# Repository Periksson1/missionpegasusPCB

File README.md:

# Mission Pegasus

PCB and mechanical design files for Mission Pegasus: a Raspberry Pi Zero carrier
and an AMS AS7265x spectral sensor board, designed to mate at 90°. The repository
includes schematics, PCB layouts, custom component libraries, mechanical CAD,
modal-analysis project files, and bills of materials.

## PDF schematics

Browse the current schematics without installing KiCad:

- [Main-board schematic (PDF)](output/pdf/main-board-schematic.pdf) - Raspberry Pi, stack interface, programming, and sensor connectors.
- [Sensor-board schematic (PDF)](output/pdf/sensor-board-schematic.pdf) - AS7265x sensors, flash, and board connector.

These are vector PDF exports of the current board schematics. Zoom in for pin
labels and component values. Regenerate the PDFs whenever the source schematics change.

## 3D CAD previews

These views are rendered from the KiCad PCB files and their associated 3D models.

### Main board

[Open the main-board project](main-board/Mission%20Pegasus.kicad_pro).

### Sensor board

[Open the sensor-board project](mezzanine-board/sensorPCB.kicad_pro).
For the mechanical assembly, see the [STEP export](CAD/PCBAssemblyFEA.stp)
and [Inventor CAD files](CAD/).

## Current design and status

The current design is on **[`main`](https://github.com/Periksson1/missionpegasusPCB/tree/main)**.
This is the default branch shown when you open the repository on GitHub.

Both boards have KiCad schematics and PCB layouts. CAD assemblies and an ANSYS
modal-analysis project are included. Manufacturing, assembly, electrical test,
and analysis pass/fail results are **not documented here yet**; the presence of
these files does not establish that the hardware has been validated.

## Getting started

1. Install **KiCad 10.0 or newer**. Both PCB files were saved with KiCad 10.0.
2. Clone the current design:

   ```sh
   git clone --branch main https://github.com/Periksson1/missionpegasusPCB.git
   cd missionpegasusPCB
   ```

3. Open `main-board/Mission Pegasus.kicad_pro` or
   `mezzanine-board/sensorPCB.kicad_pro` in KiCad's project manager.
4. Keep the project folders and their `libraries/` directories together. Custom
   library tables use `${KIPRJMOD}` paths; standard KiCad libraries are also needed.

For mechanical work, `.iam` and `.ipt` files are Autodesk Inventor assemblies and
parts. STEP (`.step` / `.stp`) exports are supplied for compatible CAD viewers.
`Analysis/ModalAnalysis.wbpj` is an ANSYS Workbench project; retain its adjacent
`ModalAnalysis_files/` directory. Exact Inventor and ANSYS application requirements
have not been documented.

## Boards

| Project | Description | Documentation |
|---|---|---|
| [Main board](main-board/Mission%20Pegasus.kicad_pro) | Raspberry Pi Zero carrier and stack interface | [Main-board README](main-board/README.md) |
| [Mezzanine board](mezzanine-board/sensorPCB.kicad_pro) | Spectral sensor daughterboard for the perpendicular assembly | [Mezzanine README](mezzanine-board/README.md) |

## Repository layout

| Path | Contents |
|---|---|
| `main-board/` | Main-board KiCad project, local libraries, documentation, BOMs, and CAD exports |
| `mezzanine-board/` | Sensor-board KiCad project, local libraries, BOMs, and CAD exports |
| `CAD/` | Mechanical assemblies, bracket parts, and assembly STEP export |
| `Analysis/` | ANSYS Workbench modal-analysis project and supporting files |
| `Combined BOM.xlsx` | Combined bill of materials |
| `Peter's Files/` | Additional copies of board projects, CAD, BOMs, and vendor software; use the top-level board folders for the documented workflow |
| `vendor/` | Third-party AMS dashboard software, firmware, and FTDI driver files |
| `MEZZANINE_INTERFACE.md` | Draft connector/interface planning notes with incomplete pin assignments |

The relationship and revision differences between `Peter's Files/` and the
top-level projects have not been reconciled in this documentation.

## BOMs and design references

- [Combined BOM](Combined%20BOM.xlsx)
- [Main-board BOM](main-board/Mission%20PegasusBOM.csv)
- [Sensor-board BOM](mezzanine-board/sensorPCBBOM.csv)
- [Component notes](main-board/docs/Components.docx) and [datasheets](main-board/docs/datasheets/)
- [Stack-interface schematic](main-board/StackInterface.kicad_sch)
- [Draft mezzanine interface](MEZZANINE_INTERFACE.md)
- [Mechanical assembly STEP export](CAD/PCBAssemblyFEA.stp)

BOMs and CAD exports are saved snapshots. Check them against the chosen board
revision before ordering parts or manufacturing. The interface document still
contains `TBD` pins; use the current schematics and verify connector numbering
and mechanical orientation before connecting hardware.

## Editing the designs

The main-board schematic contains cached versions of `AS72652`, `AS72653`, and
`RASPBERRY_PI_ZERO_2_W`. As noted in the [main-board documentation](main-board/README.md),
the corresponding library copies are older/incomplete. **Do not run
Tools → Update Symbols from Library on these parts** without first reconciling
the library definitions with the schematic.

When preparing a hardware revision, record its ERC/DRC results, fabrication
revision, assembly status, and test results alongside the design so readers can
distinguish design work from validated hardware.

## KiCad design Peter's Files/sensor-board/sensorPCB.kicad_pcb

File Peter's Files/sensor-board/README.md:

# Mezzanine board (90°)

Daughterboard that mates **perpendicular** to the Mission Pegasus main board
via the shared 2x26 (2.54 mm) stack connector.

> Status: not started — create the KiCad project into this folder (see below).

## Creating the project

1. In KiCad: **File → New Project…**
2. Save it **inside this `mezzanine-board/` folder** (e.g. `Mezzanine.kicad_pro`).
   Keep "Create a new folder" **unchecked** so the files land here directly.
3. Custom parts go in the pre-made `libraries/` subfolders:
   - `libraries/footprints/` (`.pretty`)
   - `libraries/symbols/` (`.kicad_sym`)
   - `libraries/3dmodels/` (`.3dshapes`)
   Register them in this project's `fp-lib-table` / `sym-lib-table` using
   `${KIPRJMOD}/libraries/...` paths so the board stays self-contained.

## The 90° mating interface

- Use the **same connector part and pinout** as the main board's stack
  interface (see `../main-board/StackInterface.kicad_sch`). Pin 1 must meet
  pin 1.
- For the right-angle mate, typically one board carries a **right-angle**
  header and the other a vertical socket. Decide which side is which.
- Match the **connector position and board outline** so the boards align
  physically. Verify by exporting STEP from both boards and checking the
  perpendicular fit in a 3D view.

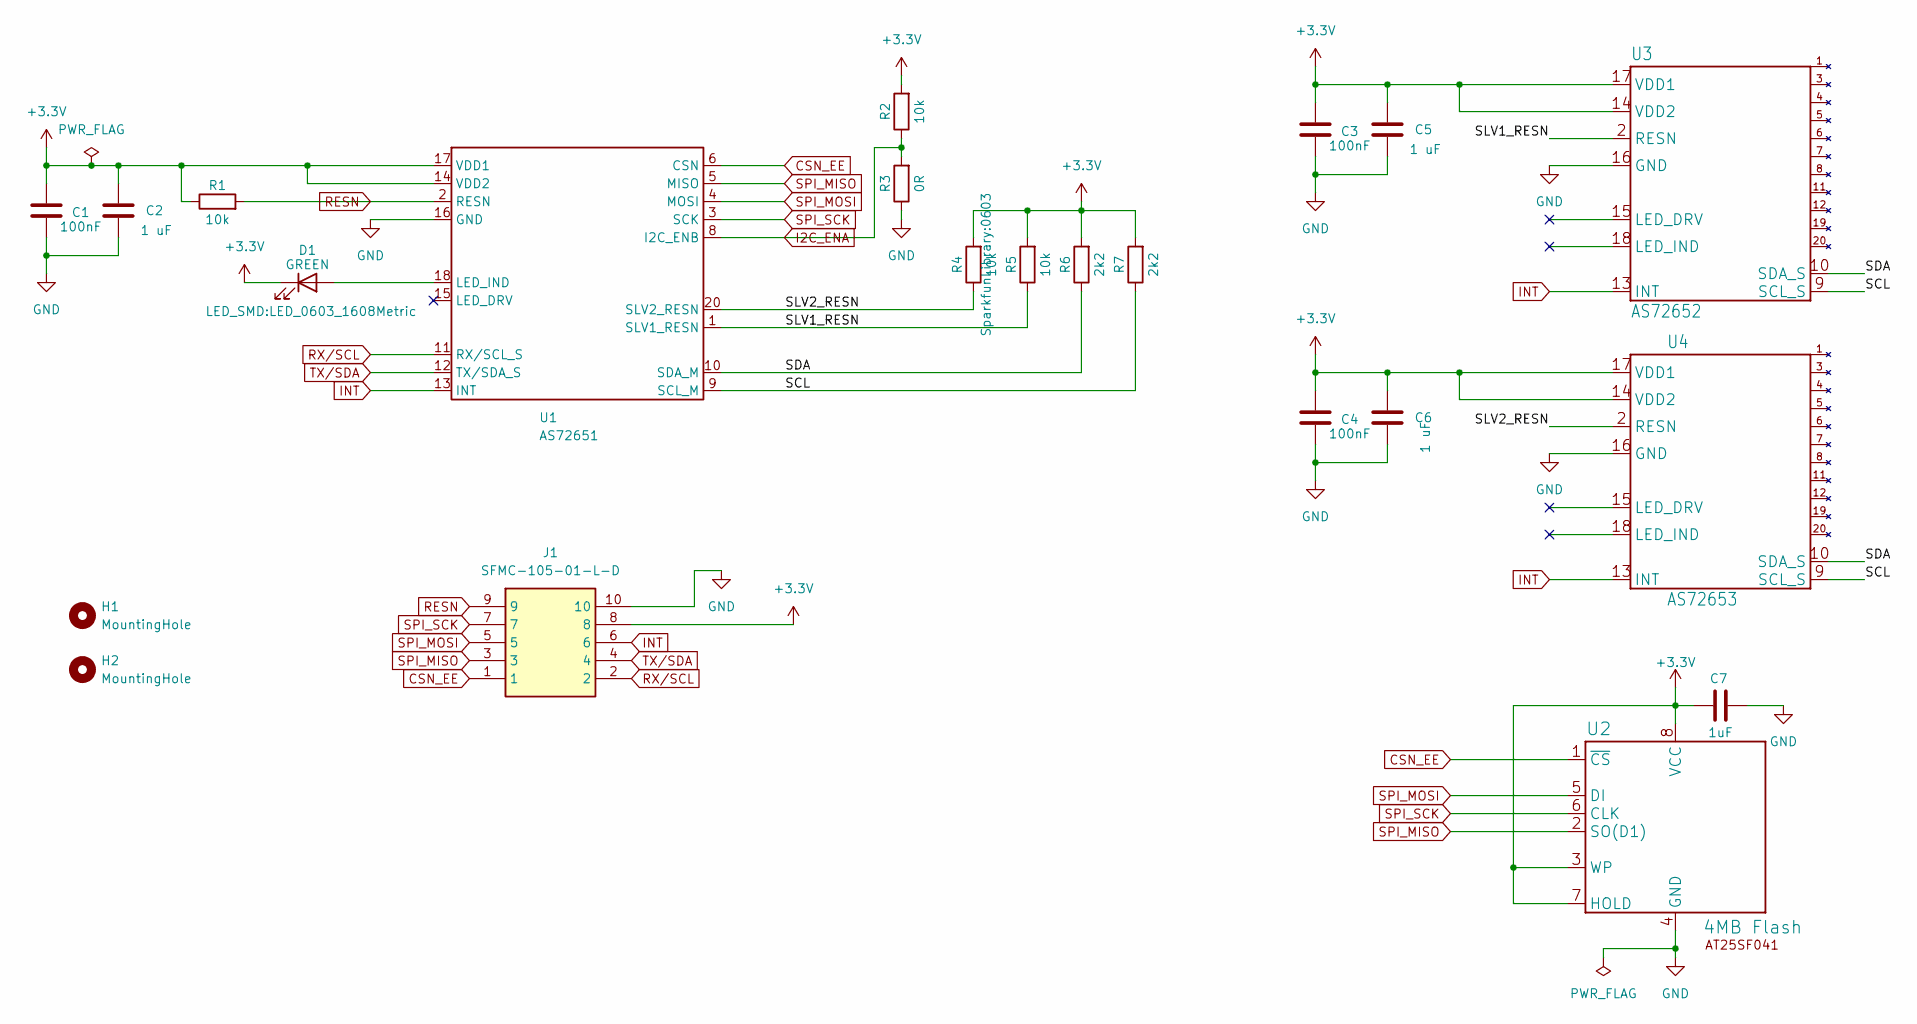
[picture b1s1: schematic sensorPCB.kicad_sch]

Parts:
C1, C3, C4: 100nF; 0603
C2, C5, C6: 1 uF; 0603
C7: 1uF; 0603
D1: GREEN; LED_0603_1608Metric
H1, H2: MountingHole; MountingHole_3.7mm
J1: SFMC-105-01-L-D; SFMC-105-XX-YY-D; Manufacturer_Part_Number SFMC-105-01-L-D; Mouser Part Number 200-SFMC10501LD
R1, R2, R4, R5: 10k; 0603
R3: 0R; 0603
R6, R7: 2k2; 0603
U1: AS72651; AS72651BLGT
U2: 4MB Flash; 4MbFlash
U3: AS72652; AS72651BLGT
U4: AS72653; AS72651BLGT

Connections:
+3.3V: C1.1, C2.1, C3.1, C4.1, C5.1, C6.1, C7.1, D1.1 (K), J1.8, R1.1, R2.2, R4.2, R5.2, R6.2, R7.2, U1.14 (VDD2), U1.17 (VDD1), U2.3 (WP), U2.7 (HOLD), U2.8 (VCC), U3.14 (VDD2), U3.17 (VDD1), U4.14 (VDD2), U4.17 (VDD1)
/SCL: R7.1, U1.9 (SCL_M), U3.9 (SCL_S), U4.9 (SCL_S)
/SDA: R6.1, U1.10 (SDA_M), U3.10 (SDA_S), U4.10 (SDA_S)
/SLV1_RESN: R5.1, U1.1 (SLV1_RESN), U3.2 (RESN)
/SLV2_RESN: R4.1, U1.20 (SLV2_RESN), U4.2 (RESN)
CSN_EE: J1.1, U1.6 (CSN), U2.1 (~CS)
GND: C1.2, C2.2, C3.2, C4.2, C5.2, C6.2, C7.2, J1.10, R3.1, U1.16 (GND), U2.4 (GND), U3.16 (GND), U4.16 (GND)
I2C_ENA: R2.1, R3.2, U1.8 (I2C_ENB)
INT: J1.6, U1.13 (INT), U3.13 (INT), U4.13 (INT)
unnamed: D1.2 (A), U1.18 (LED_IND)
RESN: J1.9, R1.2, U1.2 (RESN)
RX/SCL: J1.2, U1.11 (RX/SCL_S)
SPI_MISO: J1.3, U1.5 (MISO), U2.2 (SO(D1))
SPI_MOSI: J1.5, U1.4 (MOSI), U2.5 (DI)
SPI_SCK: J1.7, U1.3 (SCK), U2.6 (CLK)
TX/SDA: J1.4, U1.12 (TX/SDA_S)

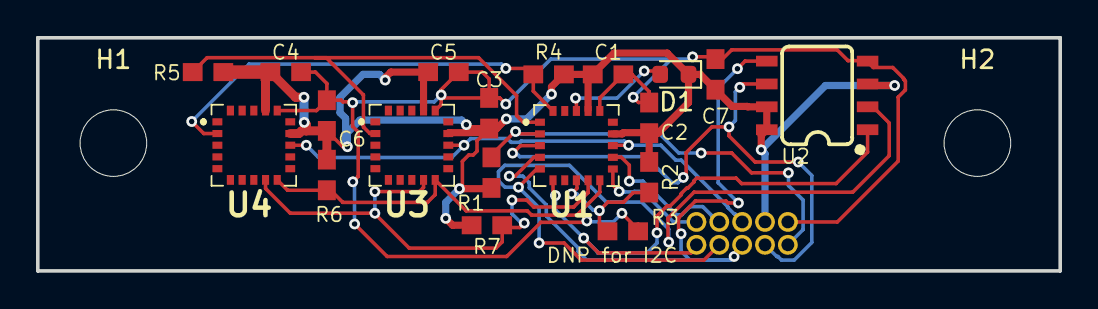
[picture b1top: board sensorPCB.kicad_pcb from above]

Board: 2 copper layers, 56.8 x 13.0 mm, 22 parts (1 on the bottom side), 16 nets.

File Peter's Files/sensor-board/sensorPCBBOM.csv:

"Reference","Qty","Value","DNP","Exclude from BOM","Exclude from Board","Footprint","Datasheet"
"C1,C3,C4","3","100nF","","","","SparkfunLibrary:0603",""
"C2,C5,C6","3","1 uF","","","","SparkfunLibrary:0603",""
"C7","1","1uF","","","","SparkfunLibrary:0603",""
"D1","1","GREEN","","","","LED_SMD:LED_0603_1608Metric",""
"J1","1","SFMC-105-01-L-D","","","","SamacSys_Parts:SFMC-105-XX-YY-D","http://suddendocs.samtec.com/prints/sfmc-1xx-xx-xx-d-xx-mkt.pdf"
"R1,R2,R4,R5","4","10k","","","","SparkfunLibrary:0603",""
"R3","1","0R","","","","SparkfunLibrary:0603",""
"R6,R7","2","2k2","","","","SparkfunLibrary:0603",""
"U1","1","AS72651","","","","SamacSys_Parts:AS72651BLGT","https://ams.com/documents/20143/36005/AS7265x_DS000612_1-00.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"
"U2","1","4MB Flash","","","","SparkfunLibrary:4MbFlash",""
"U3","1","AS72652","","","","SamacSys_Parts:AS72651BLGT",""
"U4","1","AS72653","","","","SamacSys_Parts:AS72651BLGT",""

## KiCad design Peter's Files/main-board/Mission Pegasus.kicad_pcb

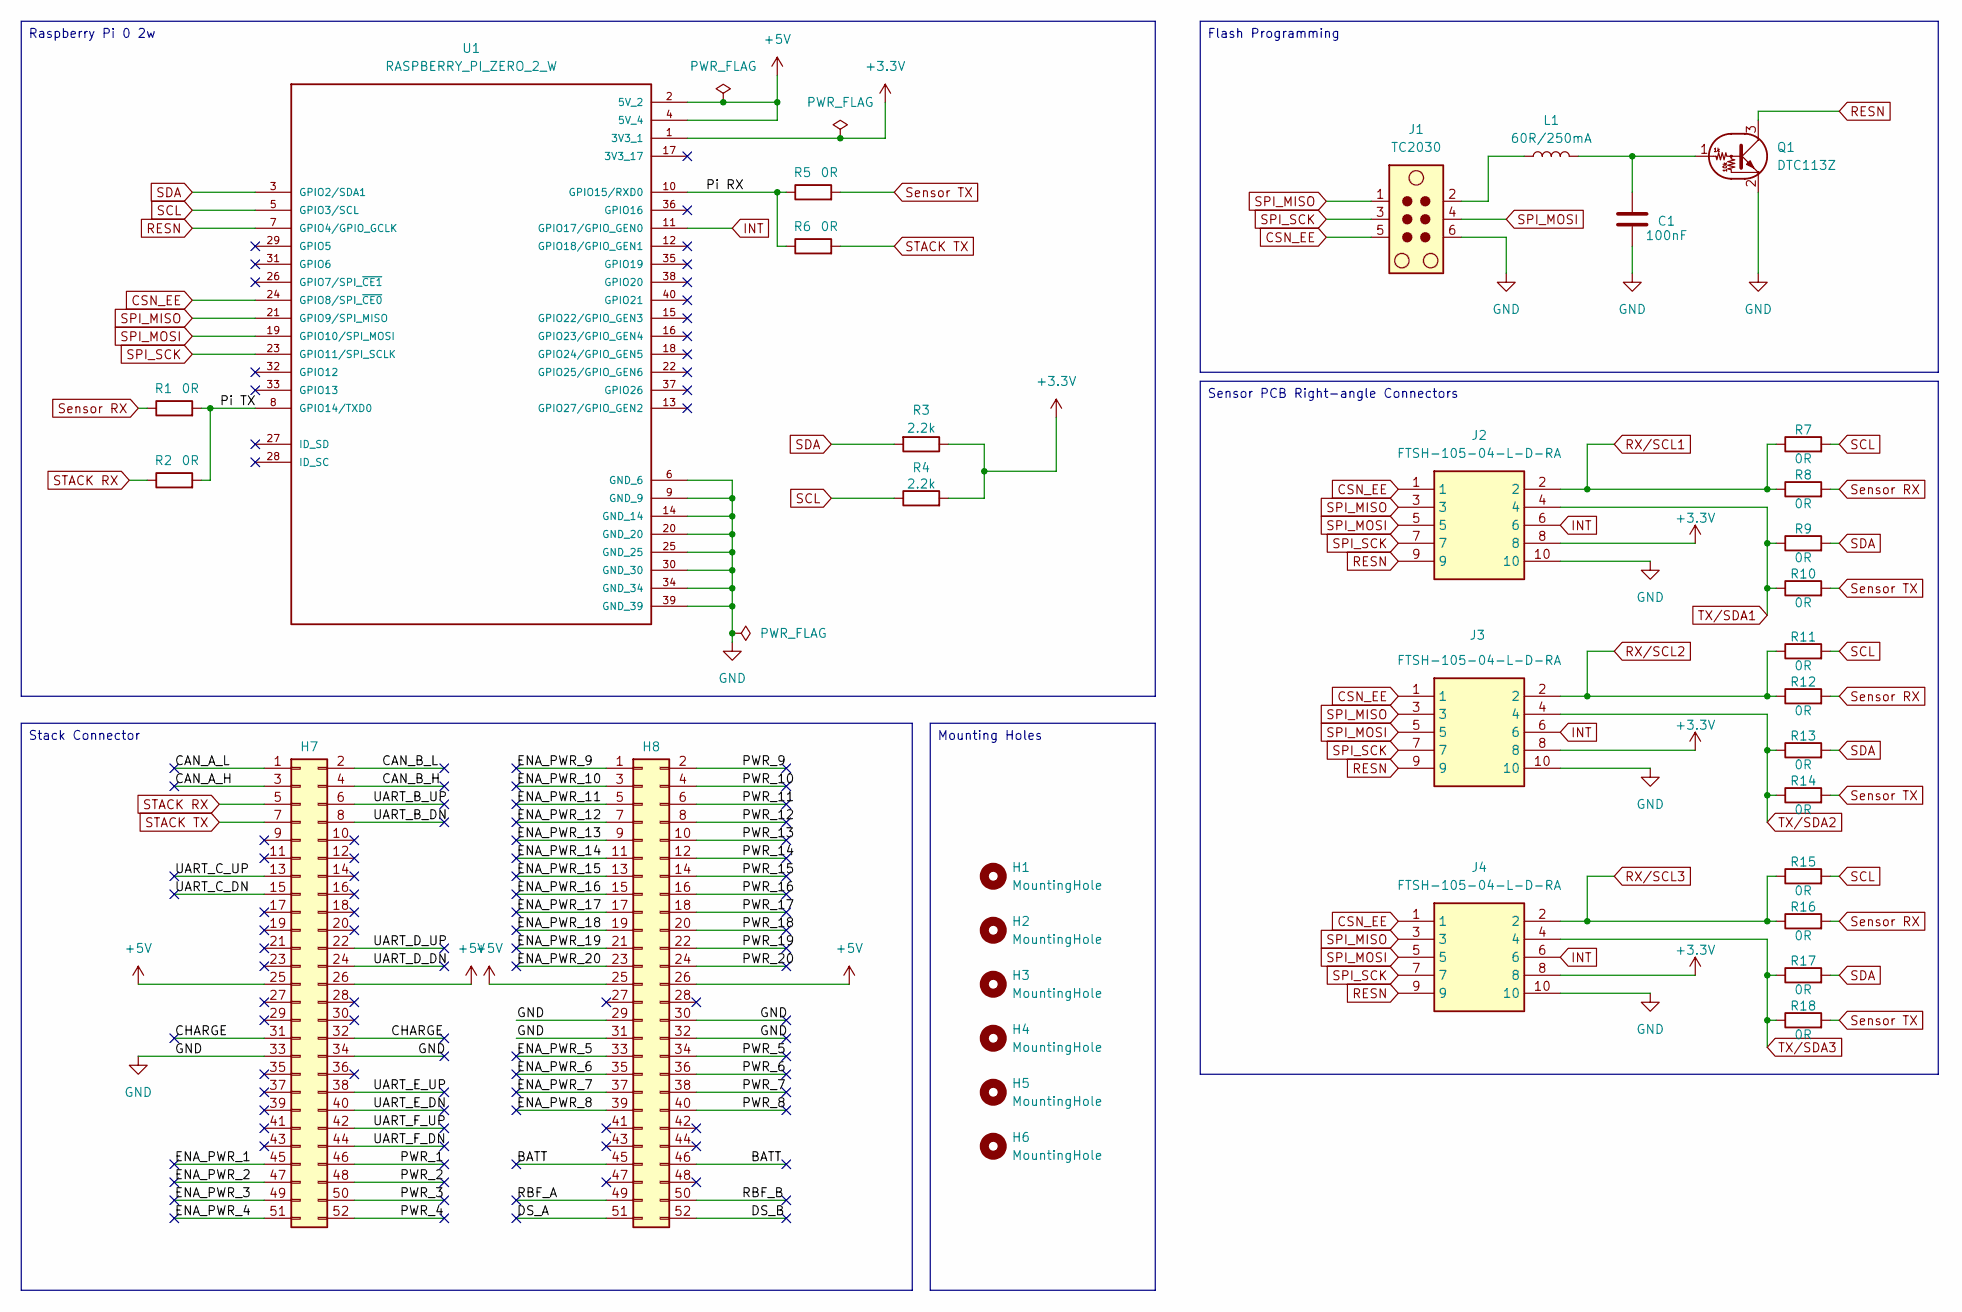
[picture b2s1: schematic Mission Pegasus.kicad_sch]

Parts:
C1: 100nF; 0603
H1, H2, H3, H4, H5, H6: MountingHole; MountingHole_3.2mm_M3
H7, H8: PC/104 Connector; PinSocket_2x26_P2.54mm_Vertical
J1: TC2030; Tag-Connect_TC2030-IDC-NL_2x03_P1.27mm_Vertical
J2, J3, J4: FTSH-105-04-L-D-RA; FTSH-105-XX-YYY-D-RA; Manufacturer_Part_Number FTSH-105-04-L-D-RA; Mouser Part Number 200-FTSH10504LDRA
L1: 60R/250mA; 0402
Q1: DTC113Z; DTC113ZUA
R1, R2, R5, R6, R7, R8, R9, R10, R11, R12, R13, R14, R15, R16, R17, R18: 0R; R_0603_1608Metric
R3, R4: 2.2k; 0603
U1: RASPBERRY_PI_ZERO_2_W; RASPBERRYPI-ZERO_RPI-ZERO; PARTREV April 2024

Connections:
+3.3V: J2.8, J3.8, J4.8, R3.1, R4.2, U1.1 (3V3_1)
+5V: H7.25, H7.26, H8.25, H8.26, U1.2 (5V_2), U1.4 (5V_4)
/BATT: H8.45, H8.46
/CAN_A_H: H7.3
/CAN_A_L: H7.1
/CAN_B_H: H7.4
/CAN_B_L: H7.2
/CHARGE: H7.31, H7.32
/DS_A: H8.51
/DS_B: H8.52
/ENA_PWR_1: H7.45
/ENA_PWR_2: H7.47
/ENA_PWR_3: H7.49
/ENA_PWR_4: H7.51
/ENA_PWR_5: H8.33
/ENA_PWR_6: H8.35
/ENA_PWR_7: H8.37
/ENA_PWR_8: H8.39
/ENA_PWR_9: H8.1
/ENA_PWR_10: H8.3
/ENA_PWR_11: H8.5
/ENA_PWR_12: H8.7
/ENA_PWR_13: H8.9
/ENA_PWR_14: H8.11
/ENA_PWR_15: H8.13
/ENA_PWR_16: H8.15
/ENA_PWR_17: H8.17
/ENA_PWR_18: H8.19
/ENA_PWR_19: H8.21
/ENA_PWR_20: H8.23
/PWR_1: H7.46
/PWR_2: H7.48
/PWR_3: H7.50
/PWR_4: H7.52
/PWR_5: H8.34
/PWR_6: H8.36
/PWR_7: H8.38
/PWR_8: H8.40
/PWR_9: H8.2
/PWR_10: H8.4
/PWR_11: H8.6
/PWR_12: H8.8
/PWR_13: H8.10
/PWR_14: H8.12
/PWR_15: H8.14
/PWR_16: H8.16
/PWR_17: H8.18
/PWR_18: H8.20
/PWR_19: H8.22
/PWR_20: H8.24
/Pi RX: R5.1, R6.1, U1.10 (GPIO15/RXD0)
/Pi TX: R1.2, R2.2, U1.8 (GPIO14/TXD0)
/RBF_A: H8.49
/RBF_B: H8.50
/UART_B_DN: H7.8
/UART_B_UP: H7.6
/UART_C_DN: H7.15
/UART_C_UP: H7.13
/UART_D_DN: H7.24
/UART_D_UP: H7.22
/UART_E_DN: H7.40
/UART_E_UP: H7.38
/UART_F_DN: H7.44
/UART_F_UP: H7.42
CSN_EE: J1.5, J2.1, J3.1, J4.1, U1.24 (GPIO8/SPI_~CE0)
GND: C1.2, H7.33, H7.34, H8.29, H8.30, H8.31, H8.32, J1.6, J2.10, J3.10, J4.10, Q1.2 (E), U1.6 (GND_6), U1.9 (GND_9), U1.14 (GND_14), U1.20 (GND_20), U1.25 (GND_25), U1.30 (GND_30), U1.34 (GND_34), U1.39 (GND_39)
INT: J2.6, J3.6, J4.6, U1.11 (GPIO17/GPIO_GEN0)
unnamed: J1.2, L1.1
unnamed: C1.1, L1.2, Q1.1 (B)
RESN: J2.9, J3.9, J4.9, Q1.3 (C), U1.7 (GPIO4/GPIO_GCLK)
RX/SCL1: J2.2, R7.1, R8.1
RX/SCL2: J3.2, R11.1, R12.1
RX/SCL3: J4.2, R15.1, R16.1
SCL: R4.1, R7.2, R11.2, R15.2, U1.5 (GPIO3/SCL)
SDA: R3.2, R9.2, R13.2, R17.2, U1.3 (GPIO2/SDA1)
SPI_MISO: J1.1, J2.3, J3.3, J4.3, U1.21 (GPIO9/SPI_MISO)
SPI_MOSI: J1.4, J2.5, J3.5, J4.5, U1.19 (GPIO10/SPI_MOSI)
SPI_SCK: J1.3, J2.7, J3.7, J4.7, U1.23 (GPIO11/SPI_SCLK)
STACK RX: H7.5, R2.1
STACK TX: H7.7, R6.2
Sensor RX: R1.1, R8.2, R12.2, R16.2
Sensor TX: R5.2, R10.2, R14.2, R18.2
TX/SDA1: J2.4, R9.1, R10.1
TX/SDA2: J3.4, R13.1, R14.1
TX/SDA3: J4.4, R17.1, R18.1

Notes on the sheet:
Flash Programming
Raspberry Pi 0 2w
Mounting Holes
Stack Connector
Sensor PCB Right-angle Connectors

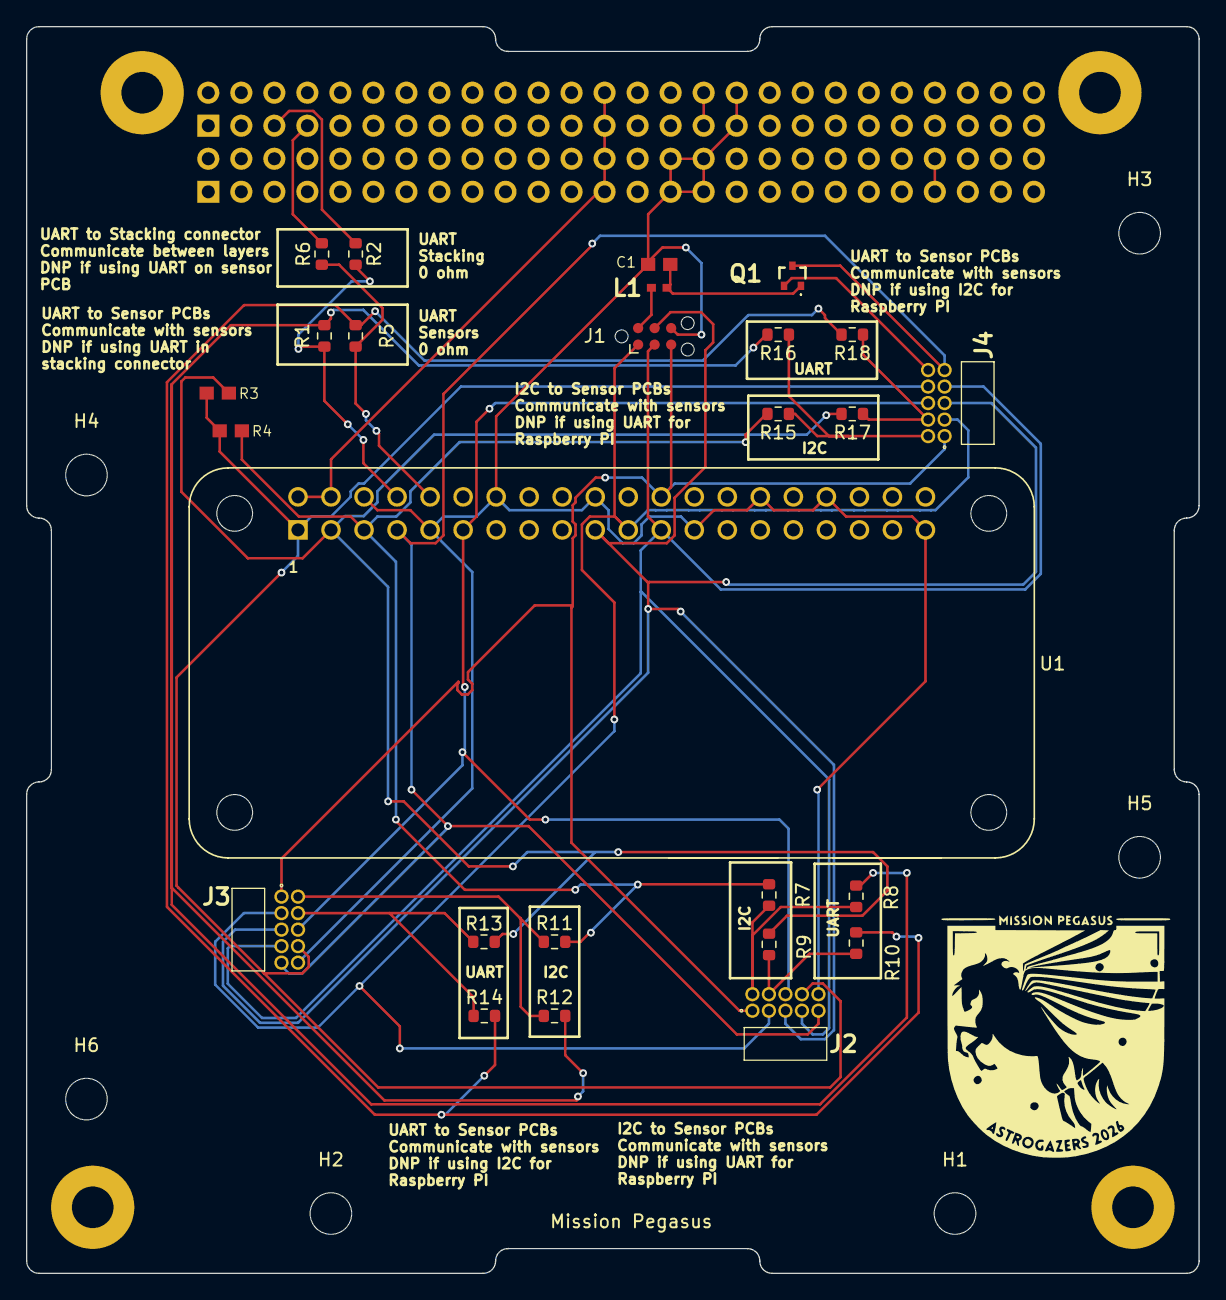
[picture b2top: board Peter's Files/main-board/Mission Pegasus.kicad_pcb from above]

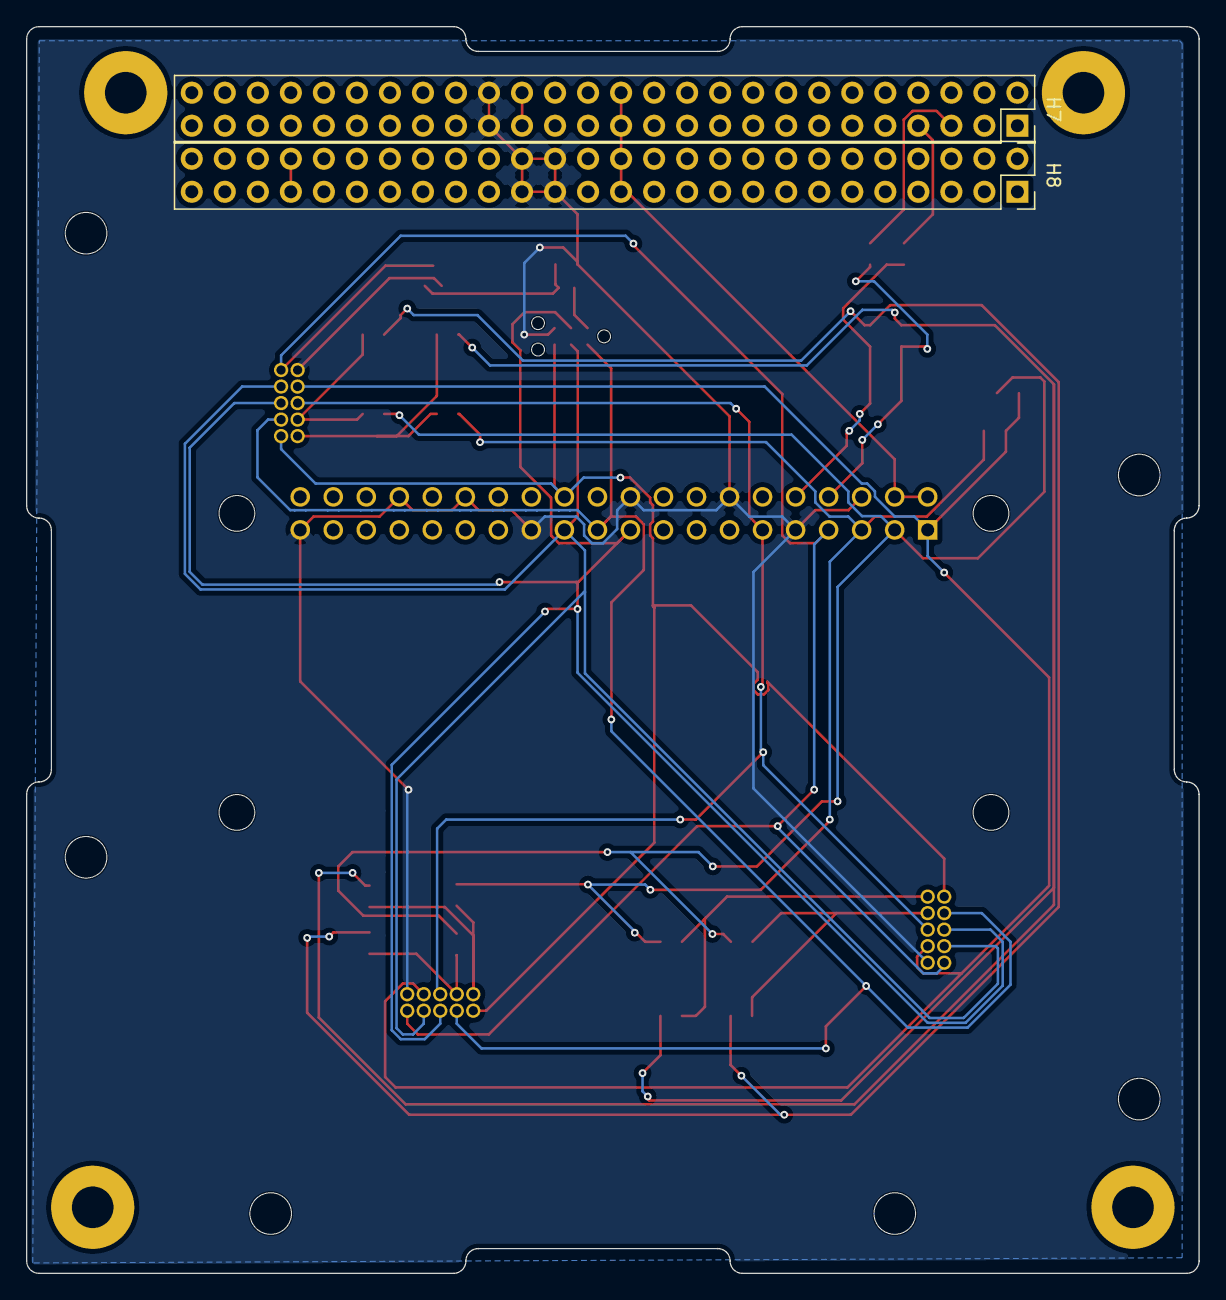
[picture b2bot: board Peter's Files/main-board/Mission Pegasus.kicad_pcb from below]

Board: 2 copper layers, 90.2 x 95.9 mm, 38 parts (2 on the bottom side), 27 nets.

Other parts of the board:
M1, M2, M3, M4: MountingHole; MountingHole_3.2mm_M3_Pad

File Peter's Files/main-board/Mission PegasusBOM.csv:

"Reference","Qty","Value","DNP","Exclude from BOM","Exclude from Board","Footprint","Datasheet","MANUFACTURER","Price"
"C1","1","100nF","","","","SparkfunLibrary:0603","","",""
"H7,H8","2","PC/104 Connector","","","","Connector_PinSocket_2.54mm:PinSocket_2x26_P2.54mm_Vertical","","",""
"J2,J3,J4","3","FTSH-105-04-L-D-RA","","","","SamacSys_Parts:FTSH-105-XX-YYY-D-RA","http://suddendocs.samtec.com/prints/ftsh-1xx-xx-xxx-dv-xxx-x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","",""
"L1","1","60R/250mA","","","","SamacSys_Parts:0402","","",""
"Q1","1","DTC113Z","","","","SamacSys_Parts:DTC113ZUA","","",""
"R1,R2,R5,R6,R7,R8,R9,R10,R11,R12,R13,R14,R15,R16,R17,R18","16","0R","","","","Resistor_SMD:R_0603_1608Metric","","",""
"R3,R4","2","2.2k","","","","SparkfunLibrary:0603","","",""
"U1","1","RASPBERRY_PI_ZERO_2_W","","","","RPIZERO:RASPBERRYPI-ZERO_RPI-ZERO","","Raspberry Pi","None"

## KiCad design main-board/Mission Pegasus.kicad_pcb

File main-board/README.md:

# Mission Pegasus main board

KiCad design for the Raspberry Pi Zero carrier and stack interface in the
Mission Pegasus two-board assembly.

[View the schematic PDF](../output/pdf/main-board-schematic.pdf).

## Opening the project

Use **KiCad 10.0 or newer** and open
[`Mission Pegasus.kicad_pro`](Mission%20Pegasus.kicad_pro).
See the [root README](../README.md) for cloning the current `main` branch.

## Files and references

| Path | Purpose |
|---|---|
| `Mission Pegasus.kicad_pro` | KiCad project settings |
| `Mission Pegasus.kicad_sch` | Root schematic |
| `Mission Pegasus.kicad_pcb` | PCB layout |
| `RPI0.kicad_sch` | Raspberry Pi Zero schematic sub-sheet |
| `StackInterface.kicad_sch` | Stack/GPIO interface sub-sheet |
| `fp-lib-table`, `sym-lib-table` | Project-local library registrations |
| `libraries/` | Custom footprints, symbols, and 3D models |
| `docs/` | Datasheets, component notes, ordering paperwork, and reference block diagram |
| `Mission PegasusBOM.csv` | Saved board BOM |
| `Images/` | Project artwork |
| `mainboard*.step`, `mainboard6/` | Mechanical exports and CAD files |

Custom library tables use `${KIPRJMOD}` paths. Keep the libraries with the
project and install the standard KiCad libraries. Third-party dashboard software,
firmware, and drivers are in [`../vendor/`](../vendor/).

## Interface and status

See the [stack schematic](StackInterface.kicad_sch) and
[draft mezzanine interface notes](../MEZZANINE_INTERFACE.md). The notes still have
incomplete pin assignments and must be checked against the current schematics.

Schematic and PCB design files are present. Manufacturing and electrical test
results are not documented. Check the [BOM](Mission%20PegasusBOM.csv) and mechanical
exports against the selected revision before using them for fabrication.

## Note on library symbols

The symbols cached in the schematics (`AS72652`, `AS72653`, and
`RASPBERRY_PI_ZERO_2_W`) are the authoritative, complete versions described by this
project's existing documentation. The library copies are older/incomplete.
**Do not run Tools → Update Symbols from Library on these parts** without first
reconciling the definitions; replacing them can break connectivity.

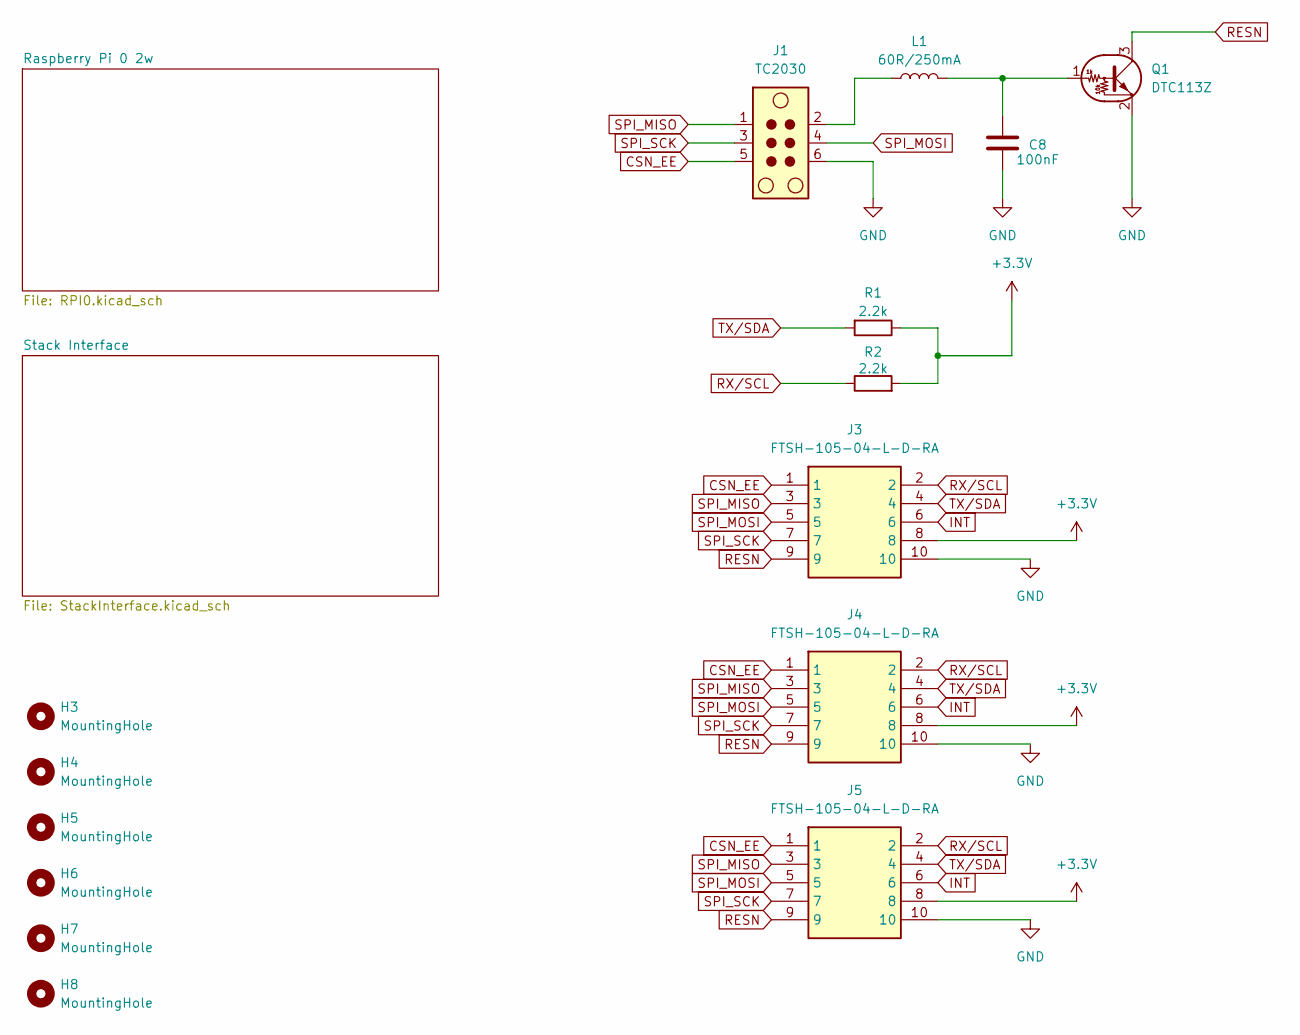
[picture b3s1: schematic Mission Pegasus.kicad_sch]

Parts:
C8: 100nF; 0603
H3, H4, H5, H6, H7, H8: MountingHole; MountingHole_3.2mm_M3
J1: TC2030; Tag-Connect_TC2030-IDC-NL_2x03_P1.27mm_Vertical
J3, J4, J5: FTSH-105-04-L-D-RA; FTSH-105-XX-YYY-D-RA; Manufacturer_Part_Number FTSH-105-04-L-D-RA; Mouser Part Number 200-FTSH10504LDRA
L1: 60R/250mA; 0402
Q1: DTC113Z; DTC113ZUA
R1, R2: 2.2k; 0603

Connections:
+3.3V: J3.8, J4.8, J5.8, R1.1, R2.2; also elsewhere on the board
CSN_EE: J1.5, J3.1, J4.1, J5.1; also elsewhere on the board
GND: C8.2, J1.6, J3.10, J4.10, J5.10, Q1.2 (E); also elsewhere on the board
INT: J3.6, J4.6, J5.6; also elsewhere on the board
unnamed: J1.2, L1.1
unnamed: C8.1, L1.2, Q1.1 (B)
RESN: J3.9, J4.9, J5.9, Q1.3 (C); also elsewhere on the board
RX/SCL: J3.2, J4.2, J5.2, R2.1; also elsewhere on the board
SPI_MISO: J1.1, J3.3, J4.3, J5.3; also elsewhere on the board
SPI_MOSI: J1.4, J3.5, J4.5, J5.5; also elsewhere on the board
SPI_SCK: J1.3, J3.7, J4.7, J5.7; also elsewhere on the board
TX/SDA: J3.4, J4.4, J5.4, R1.2; also elsewhere on the board

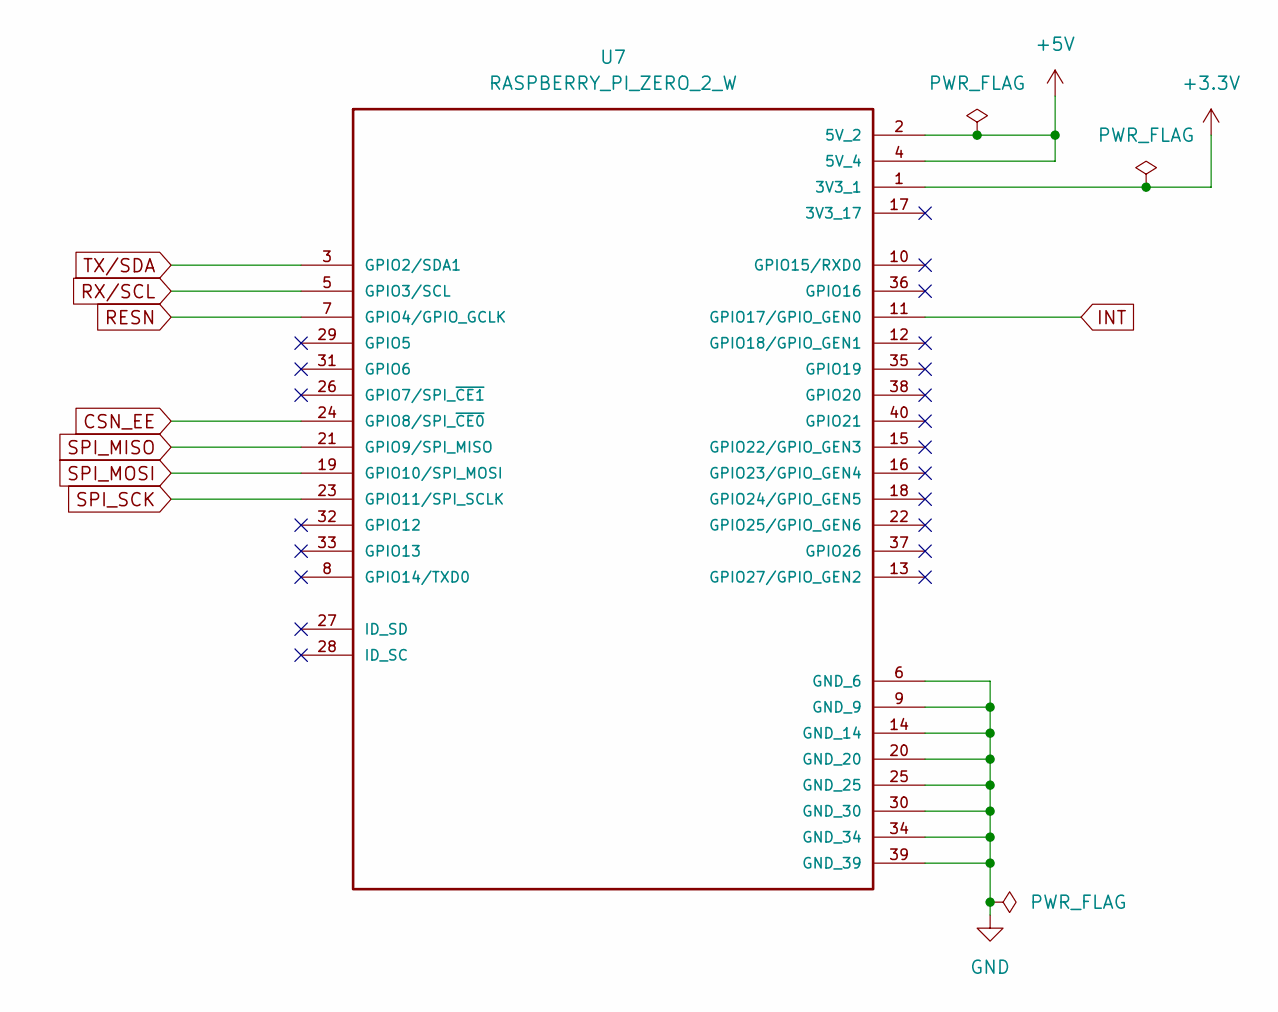
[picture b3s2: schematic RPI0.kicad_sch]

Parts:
U7: RASPBERRY_PI_ZERO_2_W; RASPBERRYPI-ZERO_RPI-ZERO; PARTREV April 2024

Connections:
+3.3V: U7.1 (3V3_1); also elsewhere on the board
+5V: U7.2 (5V_2), U7.4 (5V_4); also elsewhere on the board
CSN_EE: U7.24 (GPIO8/SPI_~CE0); also elsewhere on the board
GND: U7.6 (GND_6), U7.9 (GND_9), U7.14 (GND_14), U7.20 (GND_20), U7.25 (GND_25), U7.30 (GND_30), U7.34 (GND_34), U7.39 (GND_39); also elsewhere on the board
INT: U7.11 (GPIO17/GPIO_GEN0); also elsewhere on the board
RESN: U7.7 (GPIO4/GPIO_GCLK); also elsewhere on the board
RX/SCL: U7.5 (GPIO3/SCL); also elsewhere on the board
SPI_MISO: U7.21 (GPIO9/SPI_MISO); also elsewhere on the board
SPI_MOSI: U7.19 (GPIO10/SPI_MOSI); also elsewhere on the board
SPI_SCK: U7.23 (GPIO11/SPI_SCLK); also elsewhere on the board
TX/SDA: U7.3 (GPIO2/SDA1); also elsewhere on the board

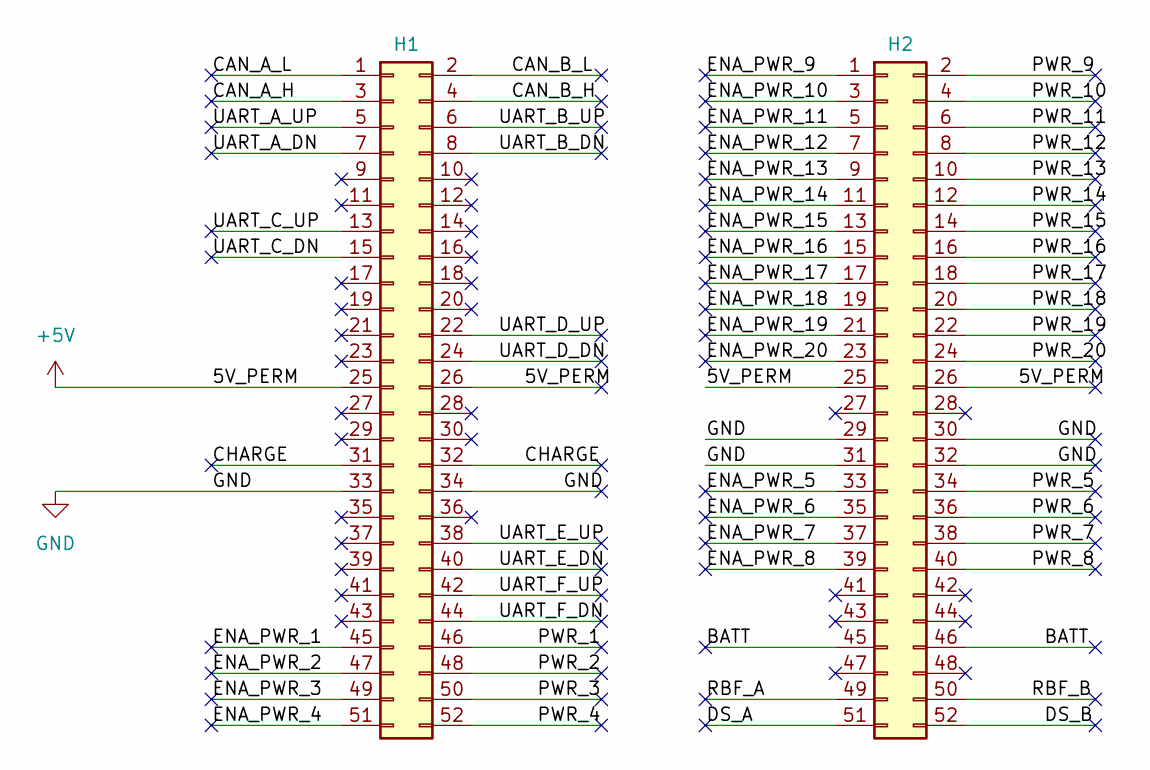
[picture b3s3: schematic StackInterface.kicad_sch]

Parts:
H1, H2: PC/104 Connector; PinSocket_2x26_P2.54mm_Vertical

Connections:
+5V: H1.25, H1.26, H2.25, H2.26; also elsewhere on the board
/Stack Interface/BATT: H2.45, H2.46
/Stack Interface/CAN_A_H: H1.3
/Stack Interface/CAN_A_L: H1.1
/Stack Interface/CAN_B_H: H1.4
/Stack Interface/CAN_B_L: H1.2
/Stack Interface/CHARGE: H1.31, H1.32
/Stack Interface/DS_A: H2.51
/Stack Interface/DS_B: H2.52
/Stack Interface/ENA_PWR_1: H1.45
/Stack Interface/ENA_PWR_2: H1.47
/Stack Interface/ENA_PWR_3: H1.49
/Stack Interface/ENA_PWR_4: H1.51
/Stack Interface/ENA_PWR_5: H2.33
/Stack Interface/ENA_PWR_6: H2.35
/Stack Interface/ENA_PWR_7: H2.37
/Stack Interface/ENA_PWR_8: H2.39
/Stack Interface/ENA_PWR_9: H2.1
/Stack Interface/ENA_PWR_10: H2.3
/Stack Interface/ENA_PWR_11: H2.5
/Stack Interface/ENA_PWR_12: H2.7
/Stack Interface/ENA_PWR_13: H2.9
/Stack Interface/ENA_PWR_14: H2.11
/Stack Interface/ENA_PWR_15: H2.13
/Stack Interface/ENA_PWR_16: H2.15
/Stack Interface/ENA_PWR_17: H2.17
/Stack Interface/ENA_PWR_18: H2.19
/Stack Interface/ENA_PWR_19: H2.21
/Stack Interface/ENA_PWR_20: H2.23
/Stack Interface/PWR_1: H1.46
/Stack Interface/PWR_2: H1.48
/Stack Interface/PWR_3: H1.50
/Stack Interface/PWR_4: H1.52
/Stack Interface/PWR_5: H2.34
/Stack Interface/PWR_6: H2.36
/Stack Interface/PWR_7: H2.38
/Stack Interface/PWR_8: H2.40
/Stack Interface/PWR_9: H2.2
/Stack Interface/PWR_10: H2.4
/Stack Interface/PWR_11: H2.6
/Stack Interface/PWR_12: H2.8
/Stack Interface/PWR_13: H2.10
/Stack Interface/PWR_14: H2.12
/Stack Interface/PWR_15: H2.14
/Stack Interface/PWR_16: H2.16
/Stack Interface/PWR_17: H2.18
/Stack Interface/PWR_18: H2.20
/Stack Interface/PWR_19: H2.22
/Stack Interface/PWR_20: H2.24
/Stack Interface/RBF_A: H2.49
/Stack Interface/RBF_B: H2.50
/Stack Interface/UART_A_DN: H1.7
/Stack Interface/UART_A_UP: H1.5
/Stack Interface/UART_B_DN: H1.8
/Stack Interface/UART_B_UP: H1.6
/Stack Interface/UART_C_DN: H1.15
/Stack Interface/UART_C_UP: H1.13
/Stack Interface/UART_D_DN: H1.24
/Stack Interface/UART_D_UP: H1.22
/Stack Interface/UART_E_DN: H1.40
/Stack Interface/UART_E_UP: H1.38
/Stack Interface/UART_F_DN: H1.44
/Stack Interface/UART_F_UP: H1.42
GND: H1.33, H1.34, H2.29, H2.30, H2.31, H2.32; also elsewhere on the board

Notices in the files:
Sparkfun/Qwiic_Spectral_Sensor-AS7265x.kicad_sch:
Released under the Creative Commons
https://creativecommons.org/licenses/by-sa/4.0
parts and their libraries:
Released under the Creative Commons Attribution Share-Alike 4.0 License
